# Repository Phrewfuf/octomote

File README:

RC-Remote

A spontaneous Project about building a custom RC-Remote.
Already contains four (yes 4) analog joysticks.
More controls in form of potentiometers and toggle-switches
are planned.
Will contain a graphical I2C display for setup and live information.

Misusing atmega16-16m (44-pin QFN package) as A/D-Converters with I2C/SPI interface
as i've got a buttload of those laying around with no use.

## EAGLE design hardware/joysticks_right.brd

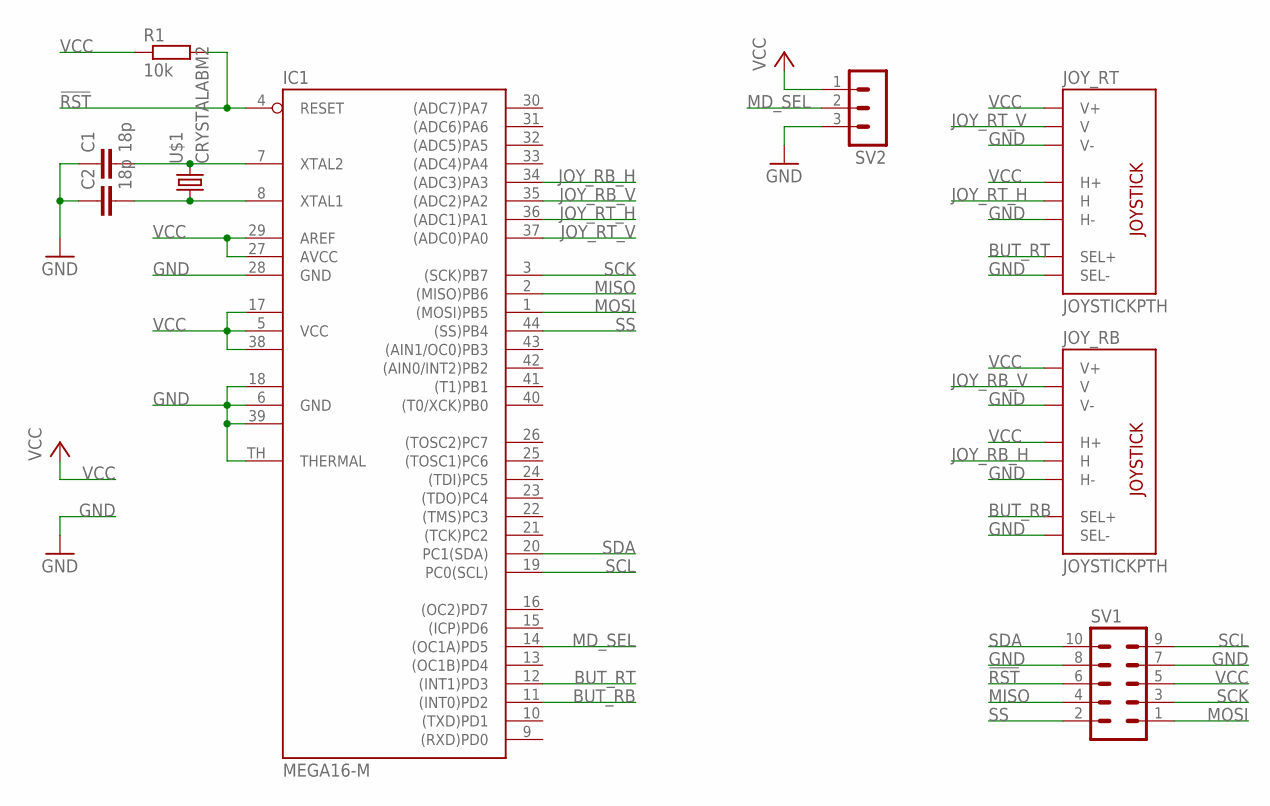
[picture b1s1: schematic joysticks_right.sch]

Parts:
C1, C2: 18p; C0603
IC1: MEGA16-M; MLF44-TH
JOY_RB: JOYSTICKPTH; JOYSTICK
JOY_RT: JOYSTICKPTH; JOYSTICK
R1: 10k; R0603
SV1: MA05-2
SV2: MA03-1
U$1: CRYSTALABM2; ABM2

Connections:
!RST: IC1.4 (RESET), R1.2, SV1.6
BUT_RB: IC1.11 ((INT0)PD2), JOY_RB.B1A (SEL+)
BUT_RT: IC1.12 ((INT1)PD3), JOY_RT.B1A (SEL+)
GND: C1.1, C2.1, IC1.6 (GND), IC1.18 (GND1), IC1.28 (GND), IC1.39 (GND2), IC1.TH (THERMAL), JOY_RB.B2A (SEL-), JOY_RB.H3 (H-), JOY_RB.V3 (V-), JOY_RT.B2A (SEL-), JOY_RT.H3 (H-), JOY_RT.V3 (V-), SV1.7, SV1.8, SV2.3
JOY_RB_H: IC1.34 ((ADC3)PA3), JOY_RB.H2 (H)
JOY_RB_V: IC1.35 ((ADC2)PA2), JOY_RB.V2 (V)
JOY_RT_H: IC1.36 ((ADC1)PA1), JOY_RT.H2 (H)
JOY_RT_V: IC1.37 ((ADC0)PA0), JOY_RT.V2 (V)
MD_SEL: IC1.14 ((OC1A)PD5), SV2.2
MISO: IC1.2 ((MISO)PB6), SV1.4
MOSI: IC1.1 ((MOSI)PB5), SV1.1
unnamed: C1.2, IC1.7 (XTAL2), U$1.P$2 (2)
unnamed: C2.2, IC1.8 (XTAL1), U$1.P$1 (1)
SCK: IC1.3 ((SCK)PB7), SV1.3
SCL: IC1.19 (PC0(SCL)), SV1.9
SDA: IC1.20 (PC1(SDA)), SV1.10
SS: IC1.44 ((SS)PB4), SV1.2
VCC: IC1.5 (VCC), IC1.17 (VCC1), IC1.27 (AVCC), IC1.29 (AREF), IC1.38 (VCC2), JOY_RB.H1 (H+), JOY_RB.V1 (V+), JOY_RT.H1 (H+), JOY_RT.V1 (V+), R1.1, SV1.5, SV2.1

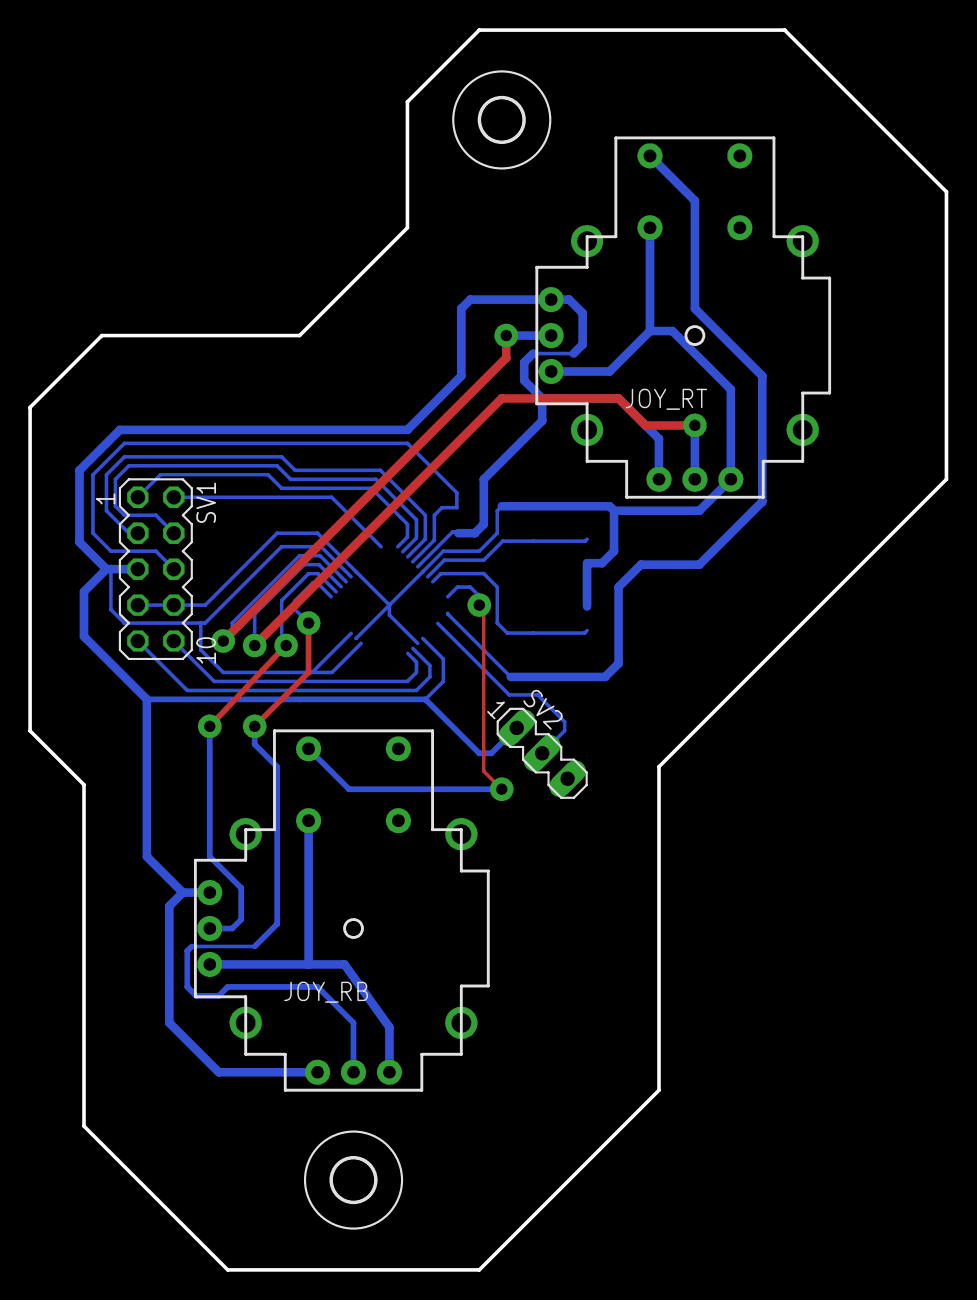
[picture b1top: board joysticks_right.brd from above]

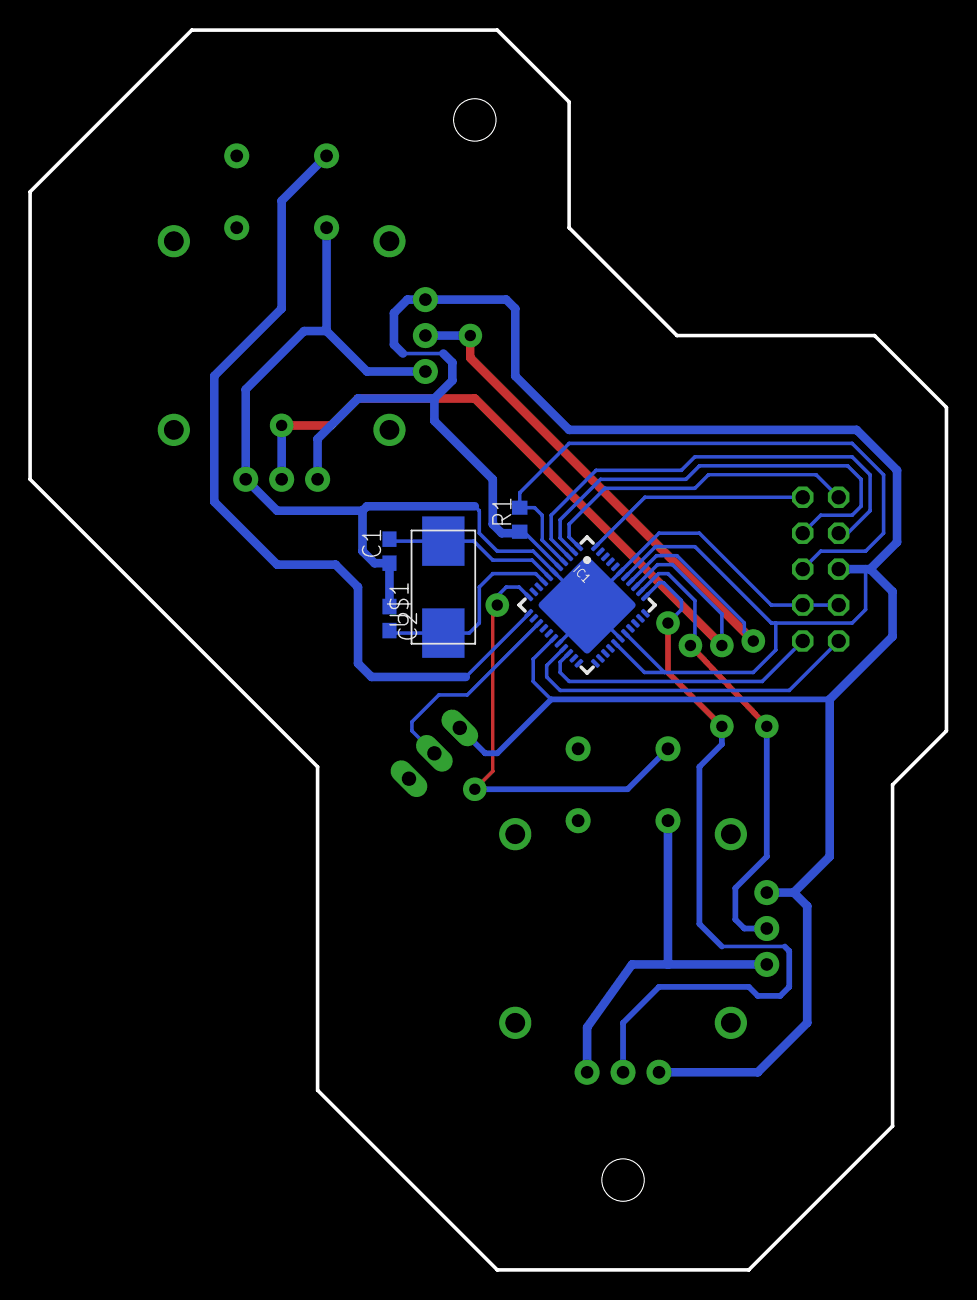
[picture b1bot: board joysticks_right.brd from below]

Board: 2 copper layers, 64.8 x 87.6 mm, 11 parts (5 on the bottom side), 18 nets.

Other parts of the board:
U$2, U$3: 3,0

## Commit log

2013-05-01 more README updates
2013-05-02 added mode selection jumper (SPI/I2C)
2013-05-02 added images for convenience
2013-05-02 bigger images
2013-05-02 some tuning to the layout
2013-05-03 minor layout tuning due to etching fuckup
2013-05-10 set value for xtal-caps
2013-05-11 created .c files for the two joystick-controllers
2013-05-11 started working on the software + added mega16 datasheet
2013-05-13 started implementing ADC routines
2013-05-15 moved some stuff to functions
2013-05-23 trying to figure out a good way to read the buttons

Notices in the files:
parts and their libraries:
SparkFun-Electromechanical: Licensing: CC v3.0 Share-Alike You are welcome to use this library for commercial purposes.
